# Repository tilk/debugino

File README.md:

# Debugino

An AVR ATmega development board with GDB debugging support via DebugWIRE.
Intended for educational purposes.

## Introduction

The Debugino board contains two microcontrollers:

 * an AVR ATmega328P (the same as in the popular Arduino Nano boards),
 * an STM32F103RBT6, which acts as the programmer, debugger and USB-to-UART.

The USB interface presents two CDC ACM virtual serial ports.
The first one allows to communicate with the UART on the ATmega.
The second implements two protocols:

* STK500v2, which allows programming the board using `avrdude` or other popular programming tools,
* GDB Remote Serial Protocol, which allows debugging using `avr-gdb`.

Programming and debugging the ATmega is performed using the DebugWIRE protocol.
Therefore no special bootloader or other software is needed on the ATmega.

To reduce component count, the board does not contain a separate crystal oscillator for the ATmega.
The clock for the ATmega is generated using a timer on the STM32, set to 18 MHz.

## Preparing a board

The STM32 is programmed via a separate ISP connector which exposes the SWDIO and SWCLK signals.

The ATmega does not require a bootloader, but the fusebits need to be changed from factory settings to enable DebugWIRE and configure the system clock.
The preferred fusebits values are:

* LFUSE 0xE0,
* HFUSE 0x9F,
* EFUSE 0xFF.

There is no ISP connector for the ATmega on the board, but the required signals are available on the pins labelled B3 (MOSI), B4 (MISO), B5 (SCK) and DWI (RESET).

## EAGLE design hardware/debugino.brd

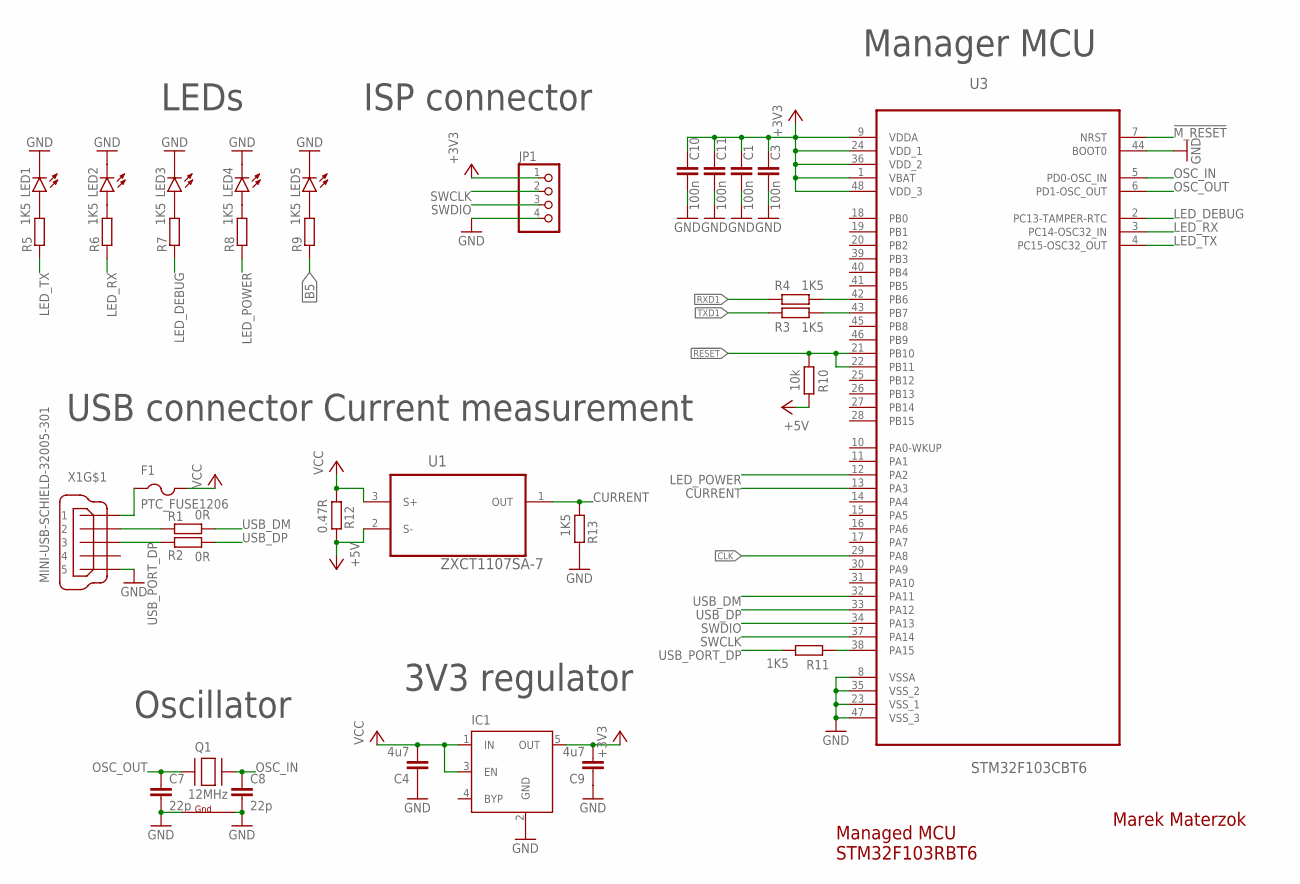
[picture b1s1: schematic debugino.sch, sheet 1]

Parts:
C1, C3, C10, C11: 100n; CAPC1008X70M
C4, C9: 4u7; CAPC1608X100M
C7, C8: 22p; CAPC1008X70M
F1: PTC_FUSE1206; FUSC3216X100M
IC1: MIC5219XX; SOT23-5
JP1: PINHD-1X4; 1X04
LED1, LED2, LED3, LED4, LED5: LEDCHIP-LED0603; CHIP-LED0603
Q1: 12MHz; NX3225
R1, R2: 0R; RESC1608X55M
R3, R4, R5, R6, R7, R8, R9, R11, R13: 1K5; RESC1608X55M
R10: 10k; RESC1608X55M
R12: 0.47R; RESC2012X65M
U1: ZXCT1107SA-7; SOT91P240X110-3N
U3: STM32F103CBT6; QFP50P900X900X160-48N
X1: MINI-USB-SCHIELD-32005-301; 32005-301

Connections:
!M_RESET: U3.7 (NRST)
!RESET: R10.1, U3.21 (PB10), U3.22 (PB11); also elsewhere on the board
+3V3: C1.1, C3.1, C9.2, C10.1, C11.1, IC1.5 (OUT), JP1.1, U3.1 (VBAT), U3.9 (VDDA), U3.24 (VDD_1), U3.36 (VDD_2), U3.48 (VDD_3)
+5V: R10.2, R12.2, U1.2 (S-); also elsewhere on the board
B5: R9.1; also elsewhere on the board
CLK: U3.29 (PA8); also elsewhere on the board
CURRENT: R13.1, U1.1 (OUT), U3.13 (PA3)
GND: C1.2, C3.2, C4.1, C7.2, C8.2, C9.1, C10.2, C11.2, IC1.2 (GND), JP1.4, LED1.C, LED2.C, LED3.C, LED4.C, LED5.C, Q1.2 (G2), Q1.4 (G1), R13.2, U3.8 (VSSA), U3.23 (VSS_1), U3.35 (VSS_2), U3.44 (BOOT0), U3.47 (VSS_3), X1.5; also elsewhere on the board
LED_DEBUG: R7.1, U3.2 (PC13-TAMPER-RTC)
LED_POWER: R8.1, U3.12 (PA2)
LED_RX: R6.1, U3.3 (PC14-OSC32_IN)
LED_TX: R5.1, U3.4 (PC15-OSC32_OUT)
unnamed: LED1.A, R5.2
unnamed: LED2.A, R6.2
unnamed: F1.1, X1.1
unnamed: LED3.A, R7.2
unnamed: LED4.A, R8.2
unnamed: LED5.A, R9.2
OSC_IN: C8.1, Q1.3 (X2), U3.5 (PD0-OSC_IN)
OSC_OUT: C7.1, Q1.1 (X1), U3.6 (PD1-OSC_OUT)
RXD1: R4.2; also elsewhere on the board
SWCLK: JP1.2, U3.37 (PA14)
SWDIO: JP1.3, U3.34 (PA13)
TXD1: R3.2; also elsewhere on the board
UART1_RX: R3.1, U3.43 (PB7)
UART1_TX: R4.1, U3.42 (PB6)
USB_DM: R1.2, U3.32 (PA11)
USB_DP: R2.2, U3.33 (PA12)
USB_PORT_DM: R1.1, X1.2
USB_PORT_DP: R2.1, R11.2, X1.3
USB_PULLUP: R11.1, U3.38 (PA15)
VCC: C4.2, F1.2, IC1.1 (IN), IC1.3 (EN), R12.1, U1.3 (S+)

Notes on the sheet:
LEDs
ISP connector
Oscillator
Manager MCU
USB connector
3V3 regulator
Marek Materzok
Managed MCU STM32F103RBT6
Current measurement

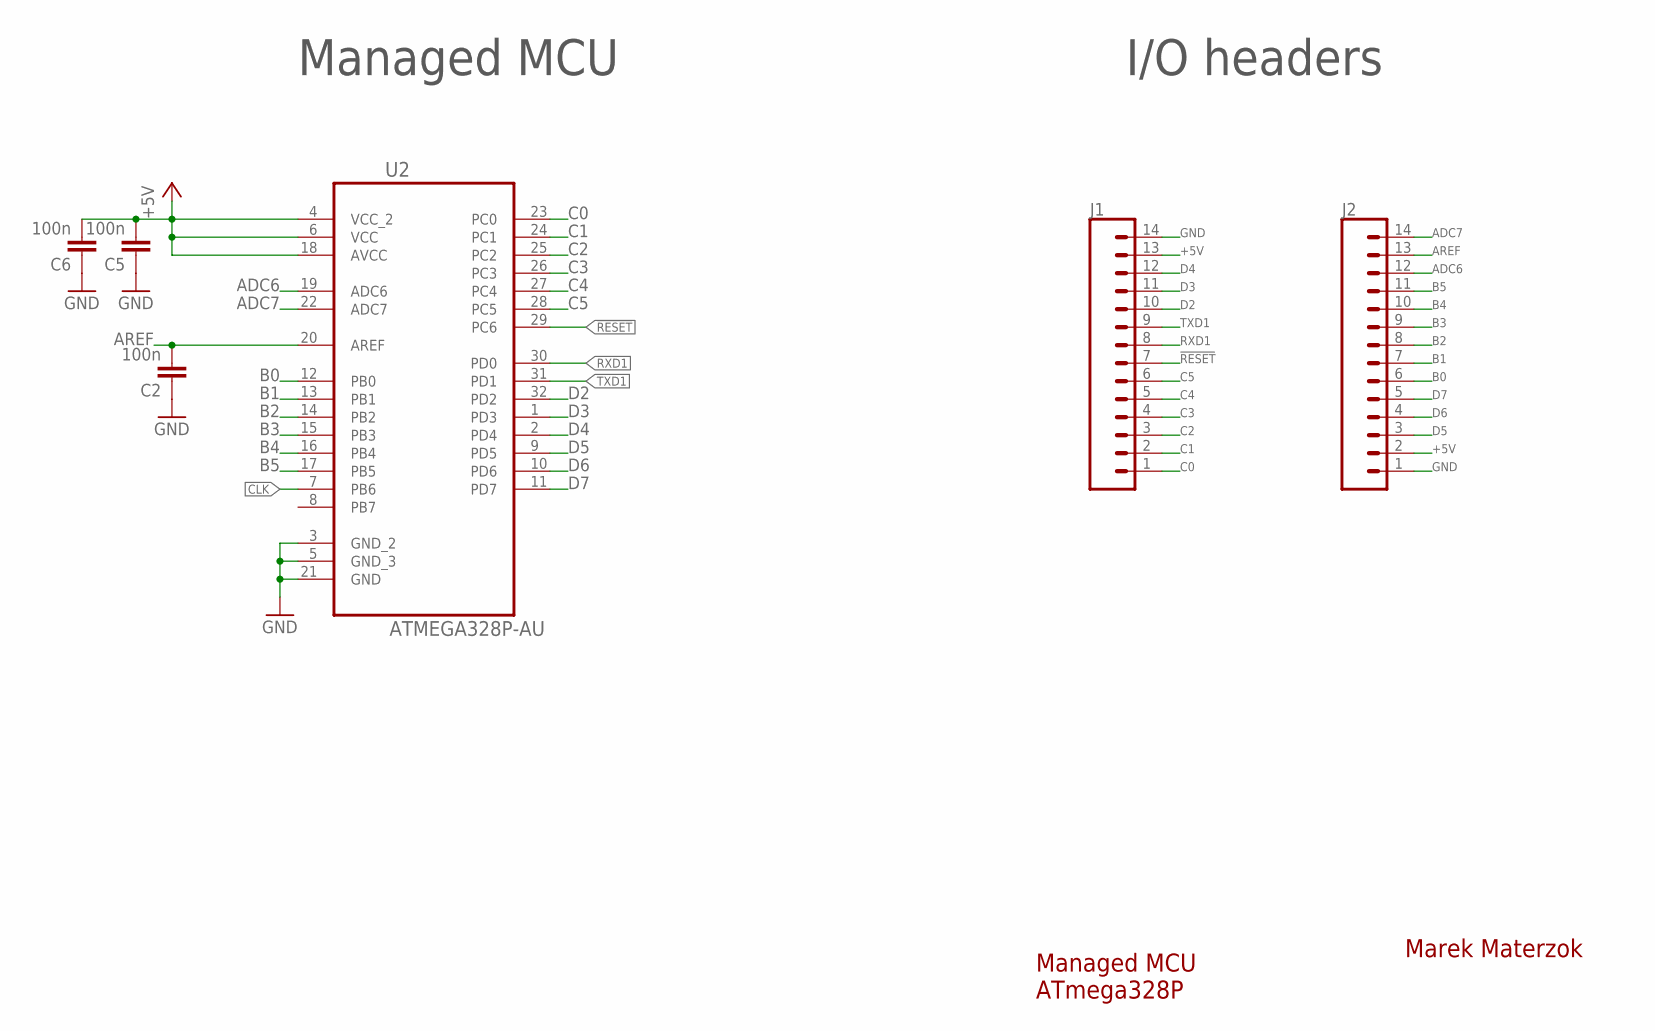
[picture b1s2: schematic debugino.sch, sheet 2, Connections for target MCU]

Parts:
C2, C5, C6: 100n; CAPC1008X70M
J1, J2: CONN_14; 1X14
U2: ATMEGA328P-AU; QFP80P900X900X120-32N

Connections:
!RESET: J1.7, U2.29 (PC6); also elsewhere on the board
+5V: C5.2, C6.2, J1.13, J2.2, U2.4 (VCC_2), U2.6 (VCC), U2.18 (AVCC); also elsewhere on the board
ADC6: J2.12, U2.19 (ADC6)
ADC7: J2.14, U2.22 (ADC7)
AREF: C2.2, J2.13, U2.20 (AREF)
B0: J2.6, U2.12 (PB0)
B1: J2.7, U2.13 (PB1)
B2: J2.8, U2.14 (PB2)
B3: J2.9, U2.15 (PB3)
B4: J2.10, U2.16 (PB4)
B5: J2.11, U2.17 (PB5); also elsewhere on the board
C0: J1.1, U2.23 (PC0)
C1: J1.2, U2.24 (PC1)
C2: J1.3, U2.25 (PC2)
C3: J1.4, U2.26 (PC3)
C4: J1.5, U2.27 (PC4)
C5: J1.6, U2.28 (PC5)
CLK: U2.7 (PB6); also elsewhere on the board
D2: J1.10, U2.32 (PD2)
D3: J1.11, U2.1 (PD3)
D4: J1.12, U2.2 (PD4)
D5: J2.3, U2.9 (PD5)
D6: J2.4, U2.10 (PD6)
D7: J2.5, U2.11 (PD7)
GND: C2.1, C5.1, C6.1, J1.14, J2.1, U2.3 (GND_2), U2.5 (GND_3), U2.21 (GND); also elsewhere on the board
RXD1: J1.8, U2.30 (PD0); also elsewhere on the board
TXD1: J1.9, U2.31 (PD1); also elsewhere on the board

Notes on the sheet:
Managed MCU
I/O headers
Marek Materzok
Managed MCU ATmega328P

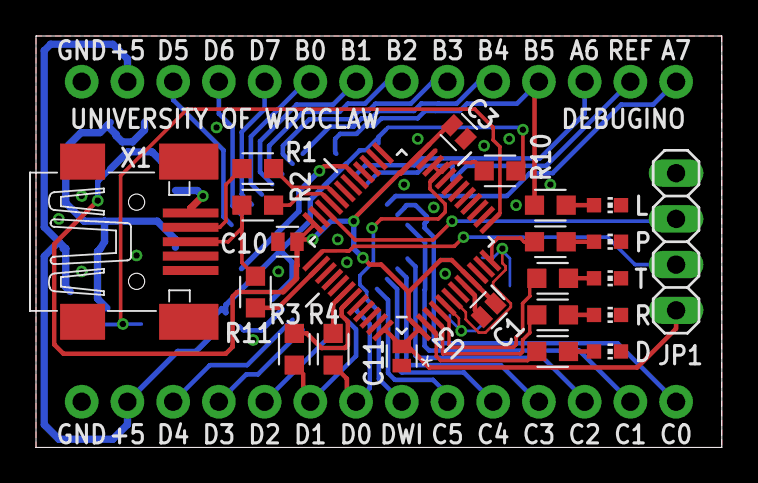
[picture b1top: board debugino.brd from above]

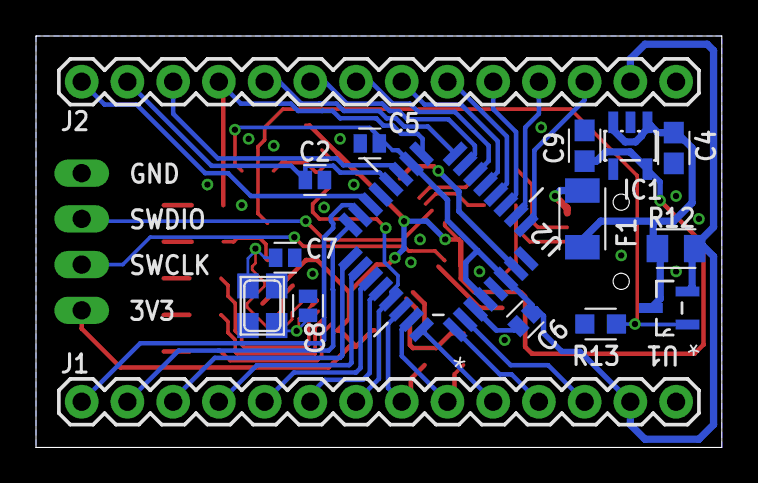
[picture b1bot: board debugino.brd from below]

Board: 2 copper layers, 38.1 x 22.9 mm, 39 parts (16 on the bottom side), 51 nets.

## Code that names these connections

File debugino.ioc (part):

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Mcu.Name=STM32F103C(8-B)Tx
Mcu.Package=LQFP48
Mcu.UserName=STM32F103CBTx
PA11.Mode=Device
PA11.Signal=USB_DM
PA12.Mode=Device
PA12.Signal=USB_DP
PA13.Mode=Serial_Wire
PA13.Signal=SYS_JTMS-SWDIO
PA14.Mode=Serial_Wire
PA14.Signal=SYS_JTCK-SWCLK
PA2.GPIOParameters=PinState,GPIO_Label
PA2.GPIO_Label=LED_POWER
PA2.PinState=GPIO_PIN_SET
PA2.Signal=GPIO_Output
PA3.GPIOParameters=GPIO_Label
PA3.GPIO_Label=CURRENT
PA3.Signal=ADCx_IN3
PA8.GPIOParameters=GPIO_Speed,GPIO_Label
PA8.GPIO_Label=CLKOUT
PA8.GPIO_Speed=GPIO_SPEED_FREQ_LOW
PA8.Signal=S_TIM1_CH1
PB10.GPIOParameters=GPIO_Label
PB10.GPIO_Label=DWIRE
PB10.Mode=Half_duplex(single_wire_mode)
PB10.Signal=USART3_TX
PB6.GPIOParameters=GPIO_Label
PB6.GPIO_Label=UART_TX
PB6.Mode=Asynchronous
PB6.Signal=USART1_TX
PB7.GPIOParameters=GPIO_Label
PB7.GPIO_Label=UART_RX
PB7.Mode=Asynchronous
PB7.Signal=USART1_RX
PC13-TAMPER-RTC.GPIOParameters=GPIO_Label
PC13-TAMPER-RTC.GPIO_Label=LED_DEBUG
PC13-TAMPER-RTC.Signal=GPIO_Output
PC14-OSC32_IN.GPIOParameters=GPIO_Label
PC14-OSC32_IN.GPIO_Label=LED_RX
PC14-OSC32_IN.Signal=GPIO_Output
PC15-OSC32_OUT.GPIOParameters=GPIO_Label
PC15-OSC32_OUT.GPIO_Label=LED_TX
PC15-OSC32_OUT.Signal=GPIO_Output
PD0-OSC_IN.Mode=HSE-External-Oscillator
PD0-OSC_IN.Signal=RCC_OSC_IN
PD1-OSC_OUT.Mode=HSE-External-Oscillator
PD1-OSC_OUT.Signal=RCC_OSC_OUT
RCC.HSE_VALUE=12000000
RCC.SYSCLKFreq_VALUE=72000000
RCC.SYSCLKSource=RCC_SYSCLKSOURCE_PLLCLK
board=custom

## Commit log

2020-10-08 First commit.
2020-10-09 Some changes.
2020-10-09 Towards dual CDC.
2020-10-12 Found endpoint setup that actually works
2020-10-12 Init FreeRTOS
2020-10-12 Towards queue-based comm
2020-10-14 Try sending larger USB packets.
2020-10-14 Kinda working transmits
2020-10-15 USB CDC with flow control (?)
2020-10-16 Towards working UART receive
2020-10-16 Fix DWIRE UART baudrate
2020-10-16 Queues for debugging task.
2020-10-16 Towards communication via stdio.
2020-10-21 Change pin mapping.
2020-10-21 Towards DebugWire
2020-10-22 Towards DWIRE flashing and break detection
2020-10-22 Generating clock signal for AVR
2020-10-22 Change DWIRE baud rate for 18MHz clock
2020-10-23 UART break handling.
2020-10-23 Prepare for main debug loop.
2020-10-23 VIM .swp files in gitignore.
2020-10-23 Initial STK500v2 support.
2020-10-23 Fix STK500v2 sync issue.
2020-10-26 Towards dumping flash via dwire.
2020-10-26 Fixed Z register handling
2020-10-26 Quick&dirty fix to USB locking on DWIRE
2020-10-28 Towards flashing
2020-10-28 Flashing is working now.
2020-10-30 Various small stuff
2020-11-02 Towards working SWD.
2020-11-04 RSP communication fix
2020-11-04 Fixes for DWIRE memory ops and SWD issues
2020-11-06 Fix silly RSP bug
2020-12-07 Towards target board.
2020-12-09 On target board, with LED support.
2020-12-09 Add continuous integration
2020-12-09 Create LICENSE
2020-12-09 Added hardware.
2020-12-11 Fixed locked debugger on serial overflow
2021-02-06 Towards current measurement.
2021-02-06 Hardware for current measurement

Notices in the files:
parts and their libraries:
SparkFun-Connectors: Licensing: Creative Commons ShareAlike 4.0 International - https://creativecommons.org/licenses/by-sa/4.0
